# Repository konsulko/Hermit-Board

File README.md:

Hermit Board
============

This is an isolator board meant for use with Atlas Scientific OEM boards.

* IMPORTANT NOTE: will unlikely work for the electroconductivity sensor due to
  the requirement the isolated ground plane to run under at least half of the
  sensor IC.

Pin mapping:

+ Pin 1 - 5V
+ Pin 2 - 5V
+ Pin 3 - VCC to buffer (NC on Rev A3)
+ Pin 4 - SDA
+ Pin 5 - INT
+ Pin 6 - SCL
+ Pin 7 - NC
+ Pin 8 - GND
+ Pin 9 - GND
+ Pin 10 - GND

Changes from v3 to v4
=====================

* Change buffer host side power supply from +5V rail to VCC
* Add VCC power plane
* Add pullup resistors to host side

Changes from v4 to v5
=====================

* Move host pullups to top side
* Add M2 screwholes
* Slightly cleanups to part placement
* Increase drill hole size for BNC connector

Changes from v5 to v6
=====================

* IMPORTANT NOTE: Do not populate the pullups R2 and R5 since INT is actually driven
* Corrected footprint for Atlas part

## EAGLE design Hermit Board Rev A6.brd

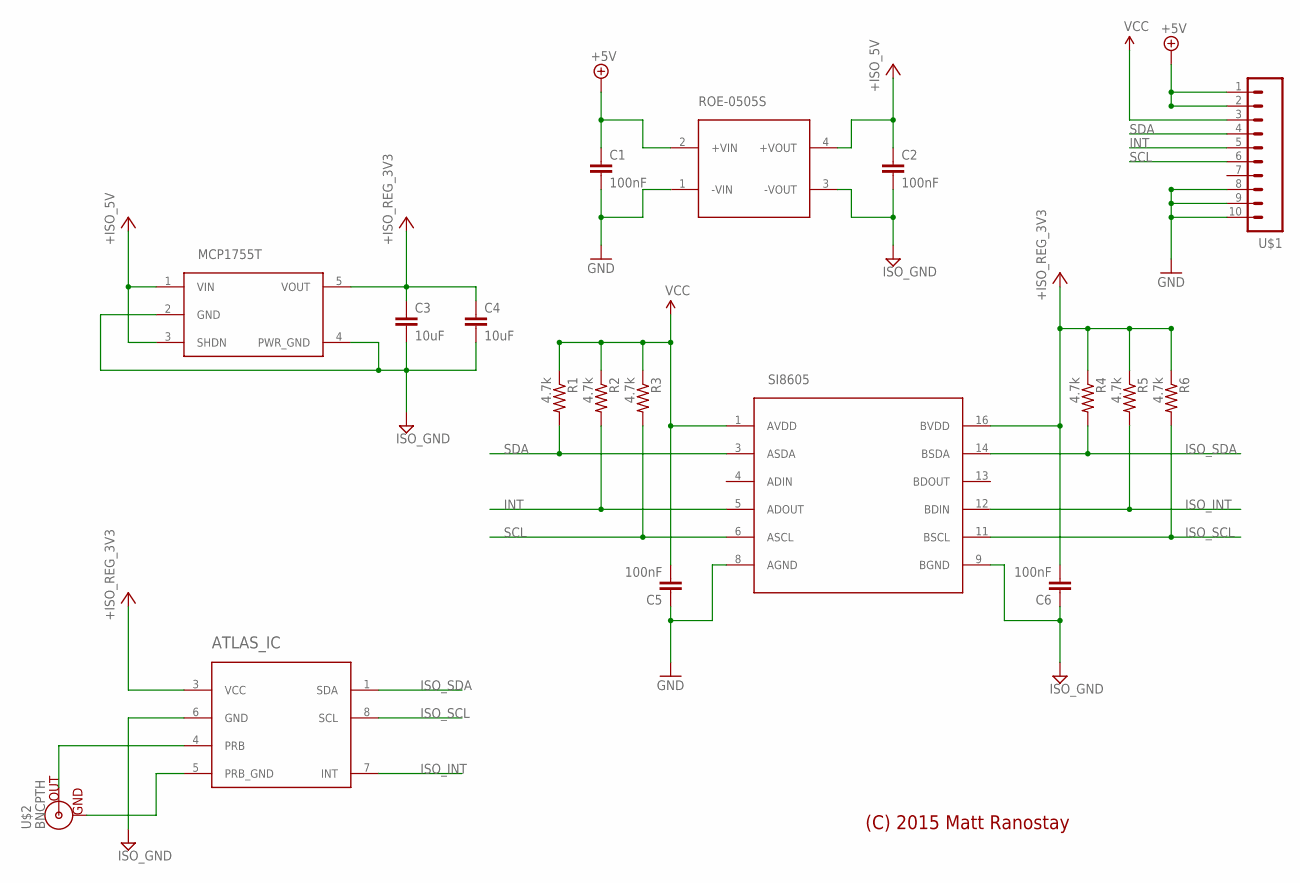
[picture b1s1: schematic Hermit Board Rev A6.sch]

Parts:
ATLAS_IC: ATLAS-OEM
C1, C2, C5, C6: 100nF; 0805
C3, C4: 10uF; 0805
MCP1755T: MCP1755T; SOT-23-5
R1, R2, R3, R4, R5, R6: 4.7k; 0805
ROE-0505S: ROE-0505S; SIP4
SI8605: SI8605; SOIC16-1.27-10X3.9MM
U$1: M10SILK_FEMALE_PTH; 1X10
U$2: BNCPTH; BNC

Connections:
+3V3: ATLAS_IC.3 (VCC), C3.1, C4.1, C6.2, MCP1755T.5 (VOUT), R4.1, R5.1, R6.1, SI8605.16 (BVDD)
+5V: C1.1, ROE-0505S.2 (+VIN), U$1.1, U$1.2
+ISO_5V: C2.1, MCP1755T.1 (VIN), MCP1755T.3 (SHDN), ROE-0505S.4 (+VOUT)
GND: C1.2, C5.1, ROE-0505S.1 (-VIN), SI8605.8 (AGND), U$1.8, U$1.9, U$1.10
INT: R2.2, SI8605.5 (ADOUT), U$1.5
ISO_GND: ATLAS_IC.6 (GND), C2.2, C3.2, C4.2, C6.1, MCP1755T.2 (GND), MCP1755T.4 (PWR_GND), ROE-0505S.3 (-VOUT), SI8605.9 (BGND)
ISO_INT: ATLAS_IC.7 (INT), R5.2, SI8605.12 (BDIN)
ISO_SCL: ATLAS_IC.8 (SCL), R6.2, SI8605.11 (BSCL)
ISO_SDA: ATLAS_IC.1 (SDA), R4.2, SI8605.14 (BSDA)
unnamed: ATLAS_IC.4 (PRB), U$2.S (OUT)
PRB_GND: ATLAS_IC.5 (PRB_GND), U$2.GND
SCL: R3.2, SI8605.6 (ASCL), U$1.6
SDA: R1.2, SI8605.3 (ASDA), U$1.4
VCC: C5.2, R1.1, R2.1, R3.1, SI8605.1 (AVDD), U$1.3

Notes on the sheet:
(C) 2015 Matt Ranostay

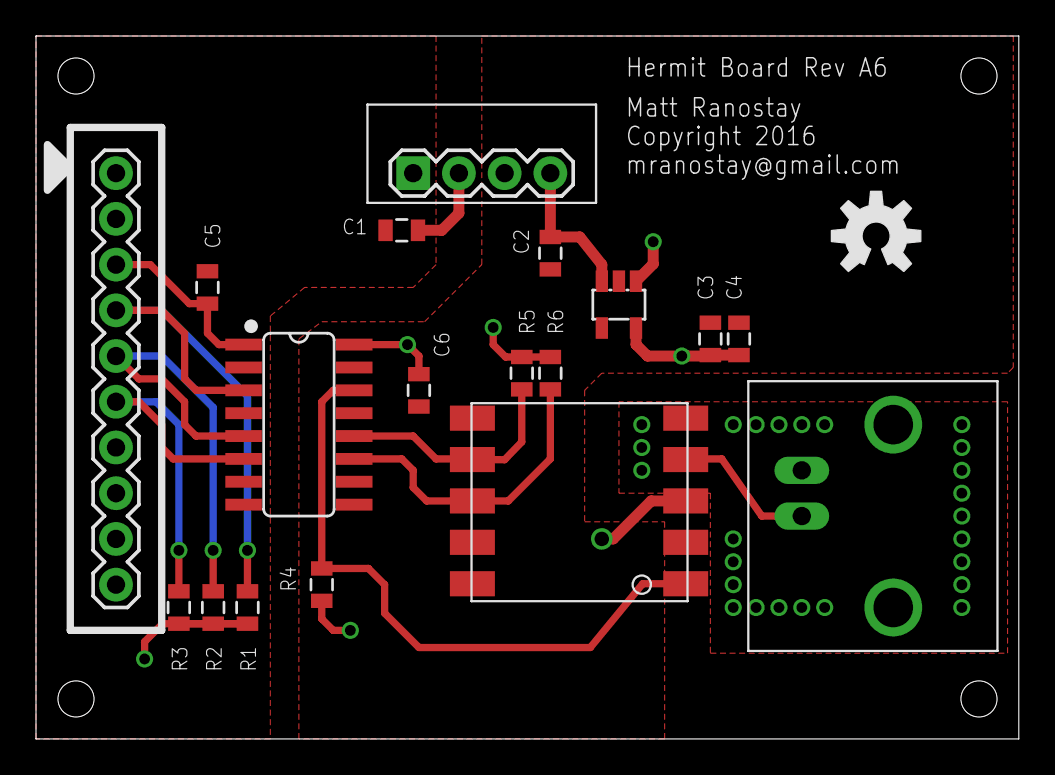
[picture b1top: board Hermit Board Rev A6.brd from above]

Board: 2 copper layers, 54.6 x 39.1 mm, 19 parts (0 on the bottom side), 14 nets.

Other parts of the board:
U$3: OSHW-LOGO-M

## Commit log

2015-12-25 Move to LICENSE.md
2015-12-25 Add BOM partlist
2016-01-02 Renamed A to A3
2016-01-02 Add Rev A4 schematic and board
2016-01-02 Add pin mapping
2016-01-04 Add Rev 5
2016-01-14 Added Hermit Board Rev A6
2016-01-18 Added pullup errata note
2016-01-23 Add pngs of board layout
2016-07-16 Note that EC sensor will unlikely work with this isolator board.

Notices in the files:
Hermit Board Rev A6.brd:
Copyright 2016
parts and their libraries:
SparkFun-Connectors: Licensing: Creative Commons ShareAlike 4.0 International - https://creativecommons.org/licenses/by-sa/4.0
